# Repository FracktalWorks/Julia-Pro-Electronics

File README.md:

# Julia-Pro-Electronics
Eagle files and documentation for Julia Pro 3D Printers

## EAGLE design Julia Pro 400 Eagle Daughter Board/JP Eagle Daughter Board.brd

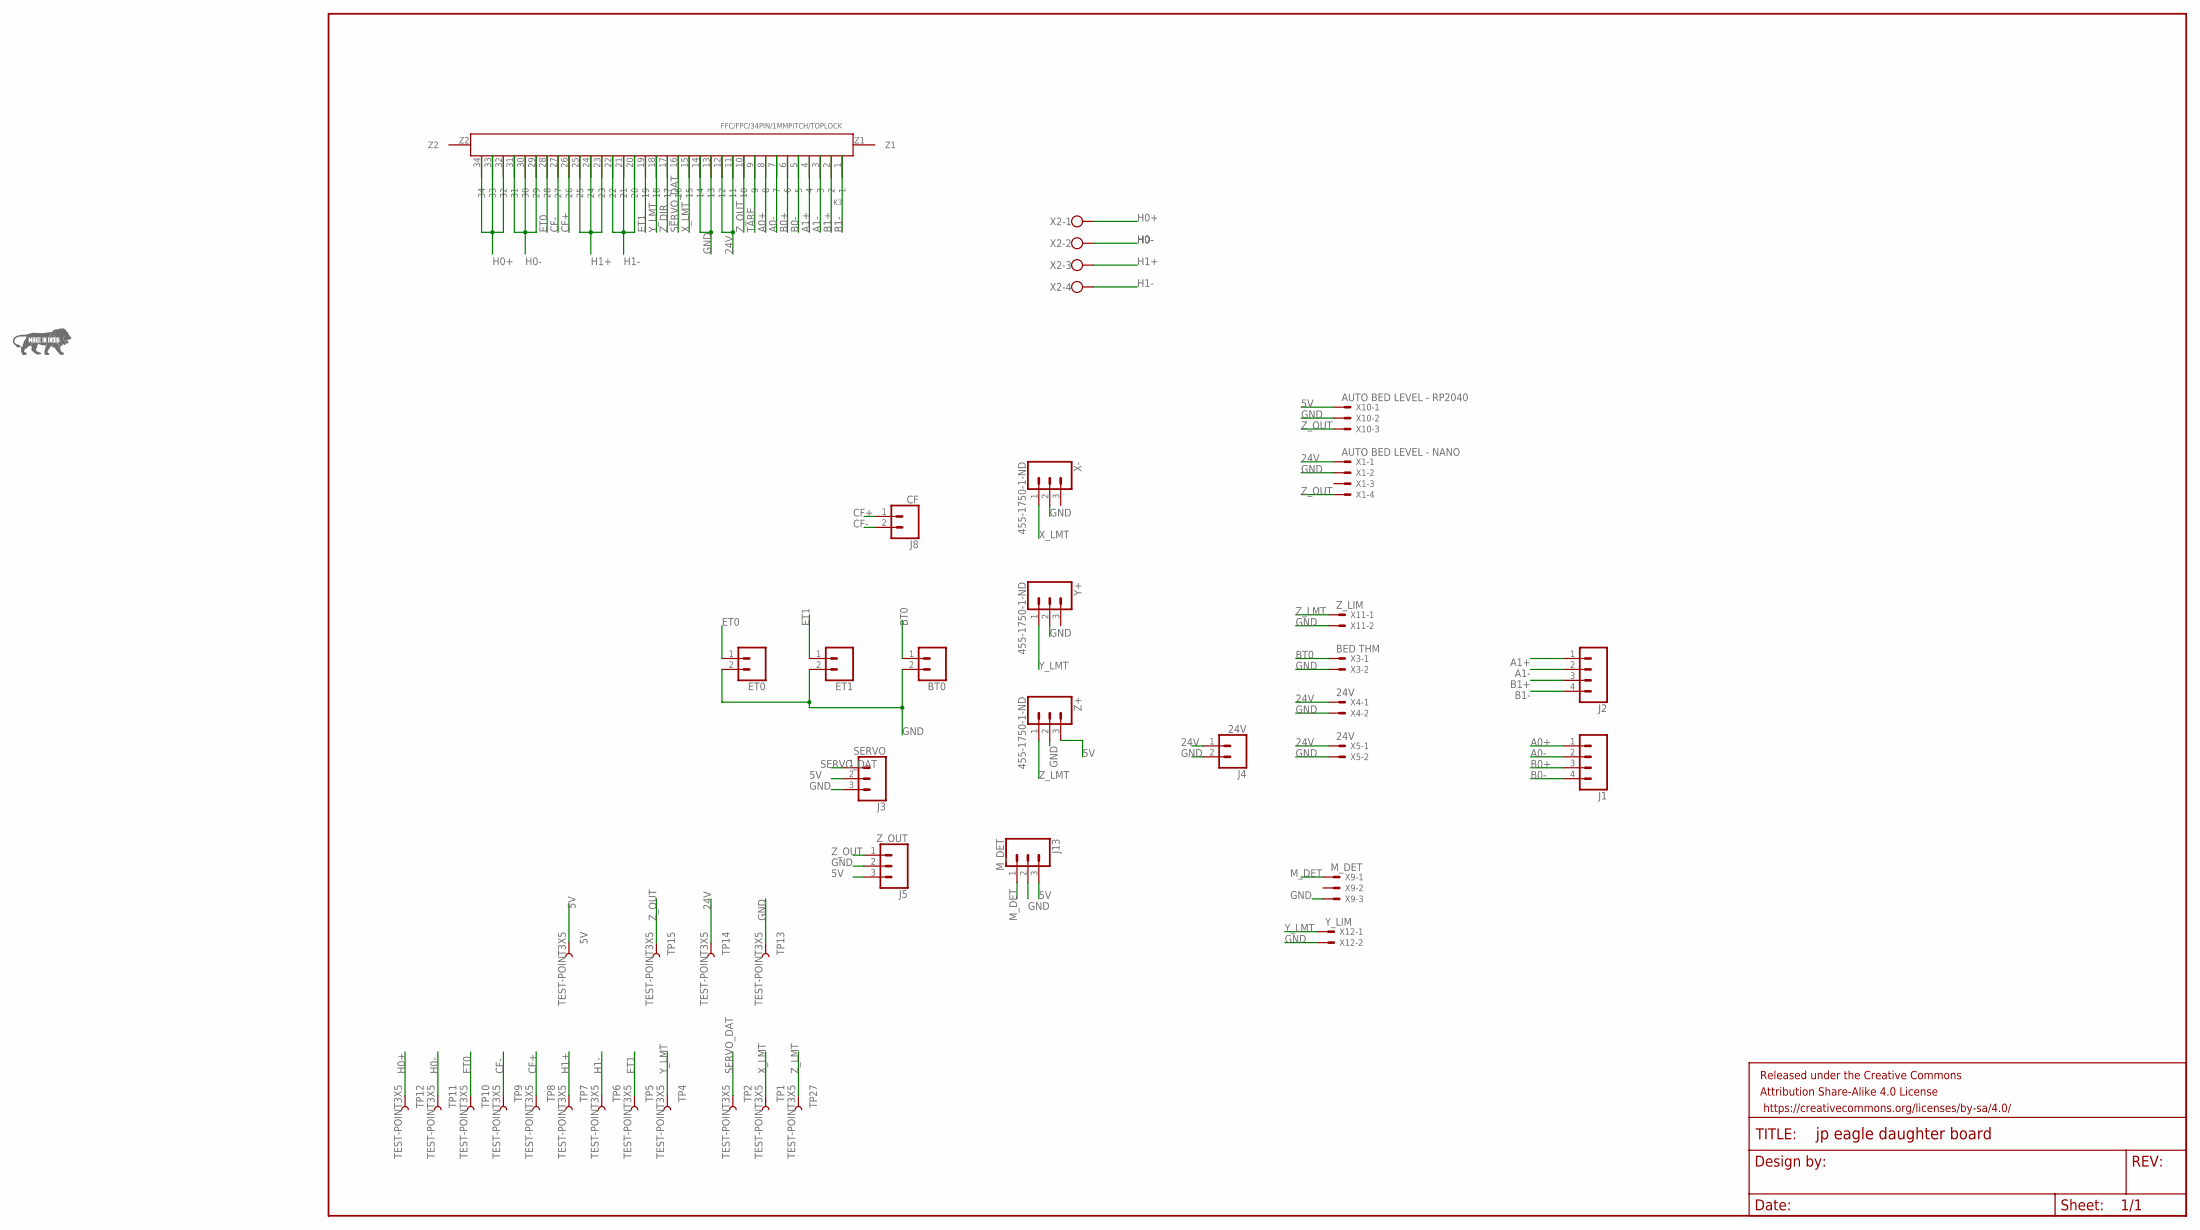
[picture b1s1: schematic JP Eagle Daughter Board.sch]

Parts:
5V: TEST-POINT3X5; PAD.03X.05
BT0: CONN_02; 1X02
ET0, ET1: CONN_02; 1X02
FRAME1: FRAME-LEDGER; CREATIVE_COMMONS
J1, J2: CONN_04; 1X04
J3: SERVO; 1X03
J4: 24V; 1X02
J5: Z_OUT; 1X03
J8: CF; 1X02
J13: M_DET; 1X03
K3: FFC/FPC/34PIN/1MMPITCH/TOPLOCK; 34PIN/1MMPITCH/FFC/FPC
TP1, TP2, TP4, TP5, TP6, TP7, TP8, TP9, TP10, TP11, TP12, TP13, TP14, TP15, TP27: TEST-POINT3X5; PAD.03X.05
U$2: MAKEININDIA
X1: AUTO BED LEVEL - NANO; JST-XH-04-PACKAGE-LONG-PAD
X2: W237-4
X3: BED THM; JST-XH-02-PACKAGE-LONG-PAD
X4, X5: 24V; JST-XH-02-PACKAGE-LONG-PAD
X9: M_DET; JST-XH-03-PACKAGE-LONG-PAD
X10: AUTO BED LEVEL - RP2040; JST-XH-03-PACKAGE-LONG-PAD
X11: Z_LIM; JST-XH-02-PACKAGE-LONG-PAD
X12: Y_LIM; JST-XH-02-PACKAGE-LONG-PAD
X-: 455-1750-1-ND; 1X03
Y+: 455-1750-1-ND; 1X03
Z+: 455-1750-1-ND; 1X03

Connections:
5V: 5V.P$1, J3.2, J5.3, J13.3, X10.1, Z+.3
24V: J4.1, K3.11, K3.12, TP14.P$1, X1.1, X4.1, X5.1
A0+: J1.1, K3.8
A0-: J1.2, K3.7
A1+: J2.1, K3.4
A1-: J2.2, K3.3
B0+: J1.3, K3.6
B0-: J1.4, K3.5
B1+: J2.3, K3.2
B1-: J2.4, K3.1
BT0: BT0.1, X3.1
CF+: J8.1, K3.26, TP8.P$1
CF-: J8.2, K3.27, TP9.P$1
ET0: ET0.1, K3.28, TP10.P$1
ET1: ET1.1, K3.19, TP5.P$1
GND: BT0.2, ET0.2, ET1.2, J3.3, J4.2, J5.2, J13.2, K3.13, K3.14, TP13.P$1, X1.2, X3.2, X4.2, X5.2, X9.3, X10.2, X11.2, X12.2, X-.2, Y+.2, Z+.2
H0+: K3.32, K3.33, K3.34, TP12.P$1, X2.1
H0-: K3.29, K3.30, K3.31, TP11.P$1, X2.2
H1+: K3.23, K3.24, K3.25, TP7.P$1, X2.3
H1-: K3.20, K3.21, K3.22, TP6.P$1, X2.4
M_DET: J13.1, X9.1
SERVO_DAT: J3.1, K3.16, TP2.P$1
TARE: K3.9
X_LMT: K3.15, TP1.P$1, X-.1
Y_LMT: K3.18, TP4.P$1, X12.1, Y+.1
Z_DIR: K3.17
Z_LMT: TP27.P$1, X11.1, Z+.1
Z_OUT: J5.1, K3.10, TP15.P$1, X1.4, X10.3

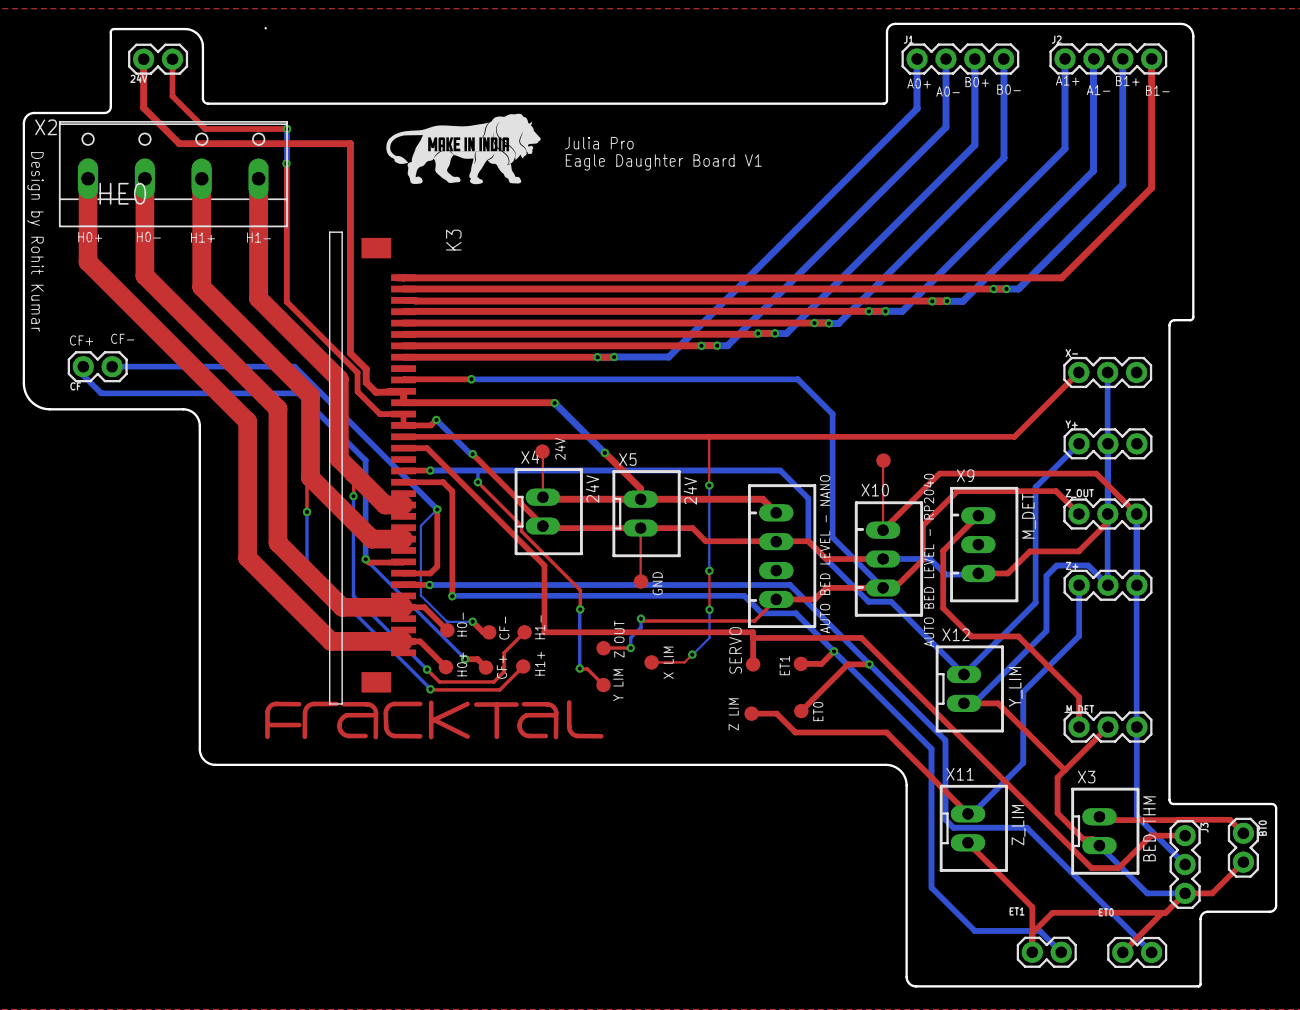
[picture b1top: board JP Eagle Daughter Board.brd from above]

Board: 2 copper layers, 110.2 x 84.7 mm, 42 parts (0 on the bottom side), 26 nets.

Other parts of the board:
U$1: FRACKTALLOGO

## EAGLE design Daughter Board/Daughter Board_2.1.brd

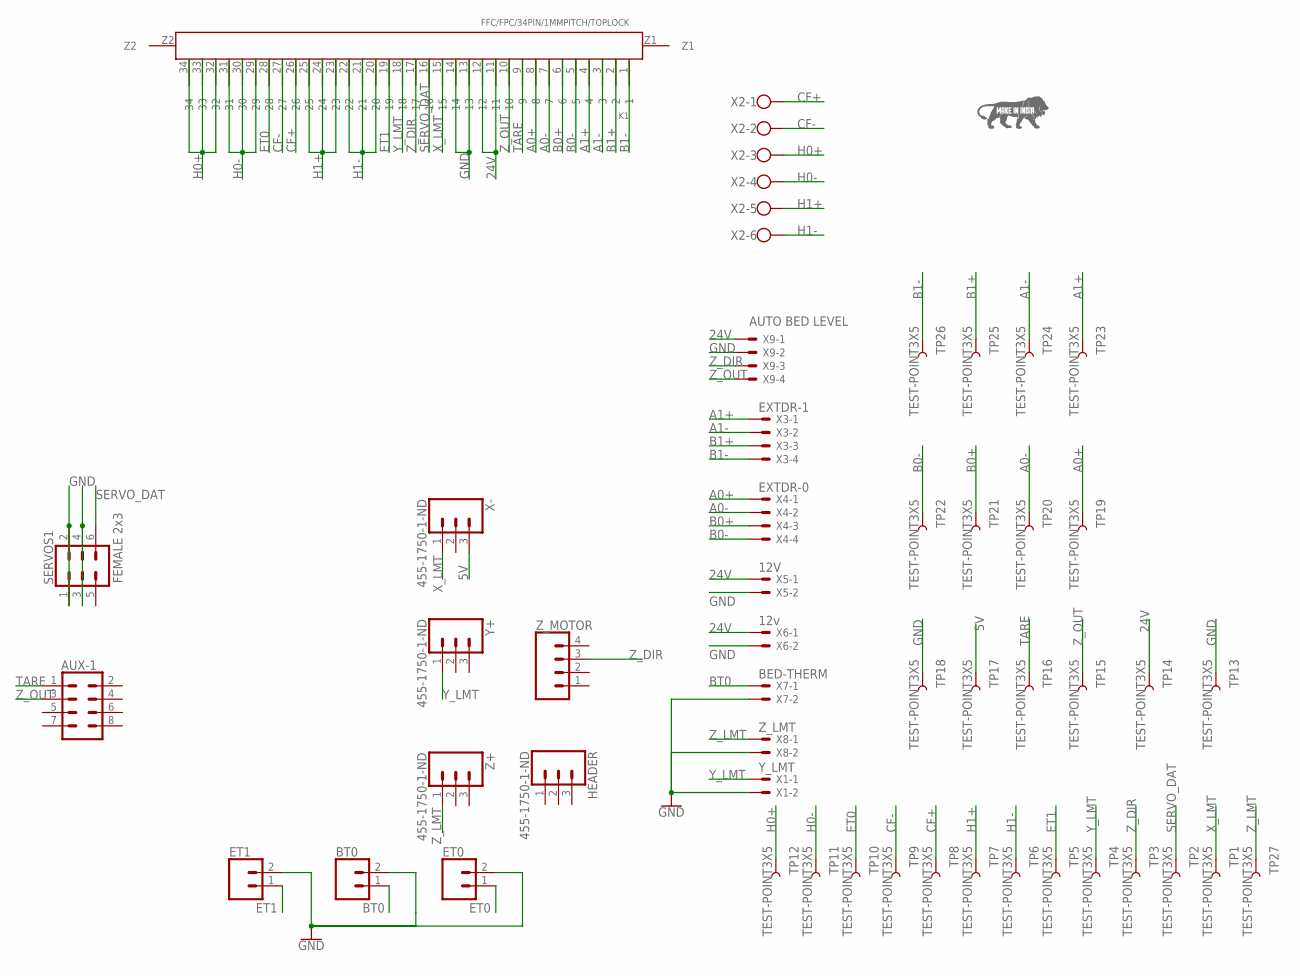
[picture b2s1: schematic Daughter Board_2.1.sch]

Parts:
AUX-1: CONN_04X2; 2X4
BT0: CONN_02; 1X02
ET0, ET1: CONN_02; 1X02
HEADER: 455-1750-1-ND; 1X03
K1: FFC/FPC/34PIN/1MMPITCH/TOPLOCK; 34PIN/1MMPITCH/FFC/FPC
SERVOS1: FEMALE 2x3; 2X3
TP1, TP2, TP3, TP4, TP5, TP6, TP7, TP8, TP9, TP10, TP11, TP12, TP13, TP14, TP15, TP16, TP17, TP18, TP19, TP20, TP21, TP22, TP23, TP24, TP25, TP26, TP27: TEST-POINT3X5; PAD.03X.05
U$2: MAKEININDIA
X1: Y_LMT; JST-XH-02-PACKAGE-LONG-PAD
X2: W237-6
X3: EXTDR-1; JST-XH-04-PACKAGE-LONG-PAD
X4: EXTDR-0; JST-XH-04-PACKAGE-LONG-PAD
X5: 12V; JST-XH-02-PACKAGE-LONG-PAD
X6: 12v; JST-XH-02-PACKAGE-LONG-PAD
X7: BED-THERM; JST-XH-02-PACKAGE-LONG-PAD
X8: Z_LMT; JST-XH-02-PACKAGE-LONG-PAD
X9: JST-XH-04-PIN-LONG-PAD; JST-XH-04-PACKAGE-LONG-PAD
X-: 455-1750-1-ND; 1X03
Y+: 455-1750-1-ND; 1X03
Z+: 455-1750-1-ND; 1X03
Z_MOTOR: CONN_04; 1X04

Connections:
5V: TP17.P$1, X-.3
24V: K1.11, K1.12, TP14.P$1, X5.1, X6.1, X9.1
A0+: K1.8, TP19.P$1, X4.1
A0-: K1.7, TP20.P$1, X4.2
A1+: K1.4, TP23.P$1, X3.1
A1-: K1.3, TP24.P$1, X3.2
B0+: K1.6, TP21.P$1, X4.3
B0-: K1.5, TP22.P$1, X4.4
B1+: K1.2, TP25.P$1, X3.3
B1-: K1.1, TP26.P$1, X3.4
BT0: BT0.1, X7.1
CF+: K1.26, TP8.P$1, X2.1
CF-: K1.27, TP9.P$1, X2.2
ET0: ET0.1, K1.28, TP10.P$1
ET1: ET1.1, K1.19, TP5.P$1
GND: BT0.2, ET0.2, ET1.2, K1.13, K1.14, SERVOS1.1, SERVOS1.2, TP13.P$1, TP18.P$1, X1.2, X5.2, X6.2, X7.2, X8.2, X9.2
H0+: K1.32, K1.33, K1.34, TP12.P$1, X2.3
H0-: K1.29, K1.30, K1.31, TP11.P$1, X2.4
H1+: K1.23, K1.24, K1.25, TP7.P$1, X2.5
H1-: K1.20, K1.21, K1.22, TP6.P$1, X2.6
unnamed: SERVOS1.3, SERVOS1.4
SERVO_DAT: K1.16, SERVOS1.6, TP2.P$1
TARE: AUX-1.1, K1.9, TP16.P$1
X_LMT: K1.15, TP1.P$1, X-.1
Y_LMT: K1.18, TP4.P$1, X1.1, Y+.1
Z_DIR: K1.17, TP3.P$1, X9.3, Z_MOTOR.3
Z_LMT: TP27.P$1, X8.1, Z+.1
Z_OUT: AUX-1.3, K1.10, TP15.P$1, X9.4

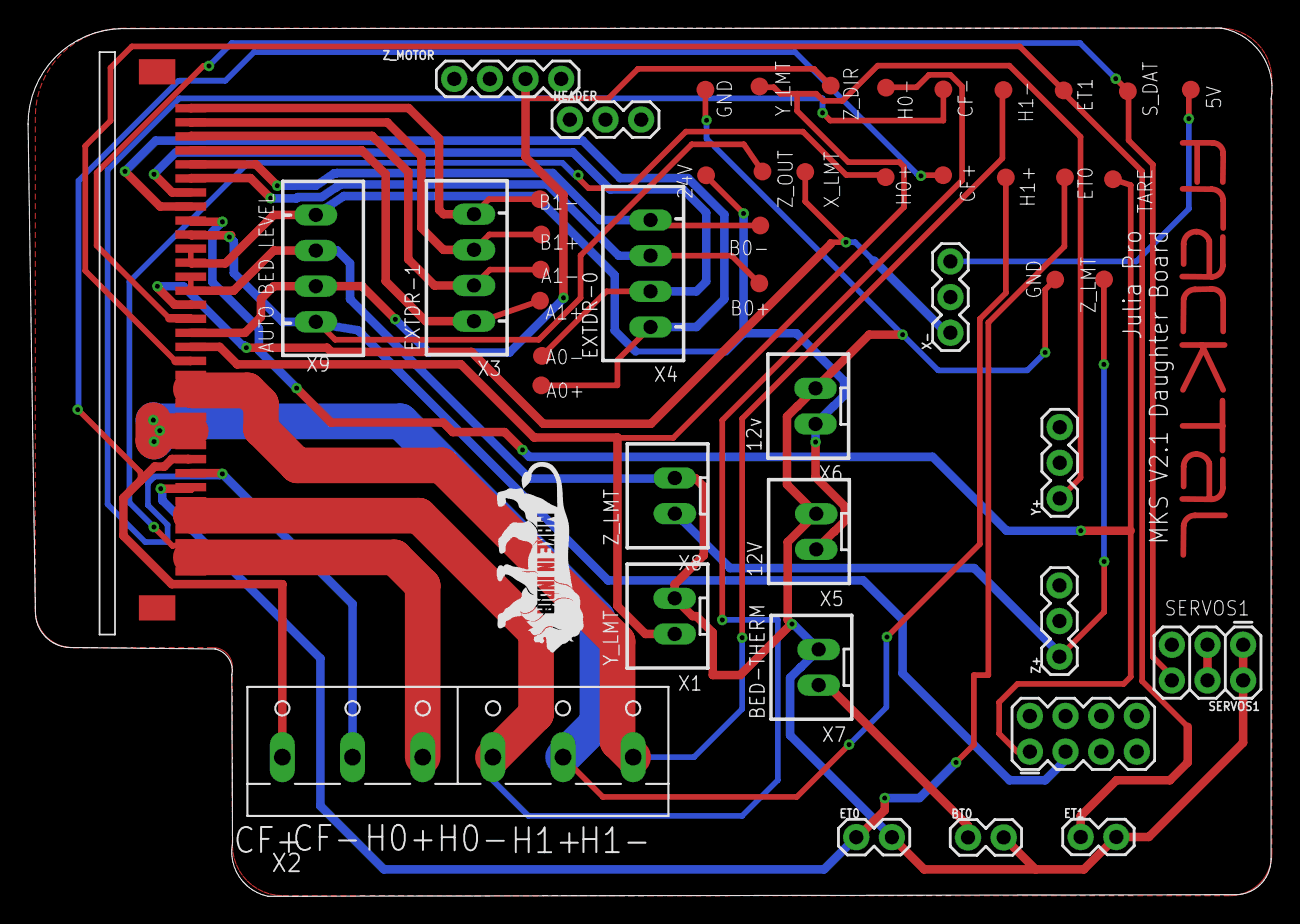
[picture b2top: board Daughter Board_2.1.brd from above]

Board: 2 copper layers, 88.6 x 61.9 mm, 49 parts (0 on the bottom side), 28 nets.

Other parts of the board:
U$1: FRACKTALLOGO

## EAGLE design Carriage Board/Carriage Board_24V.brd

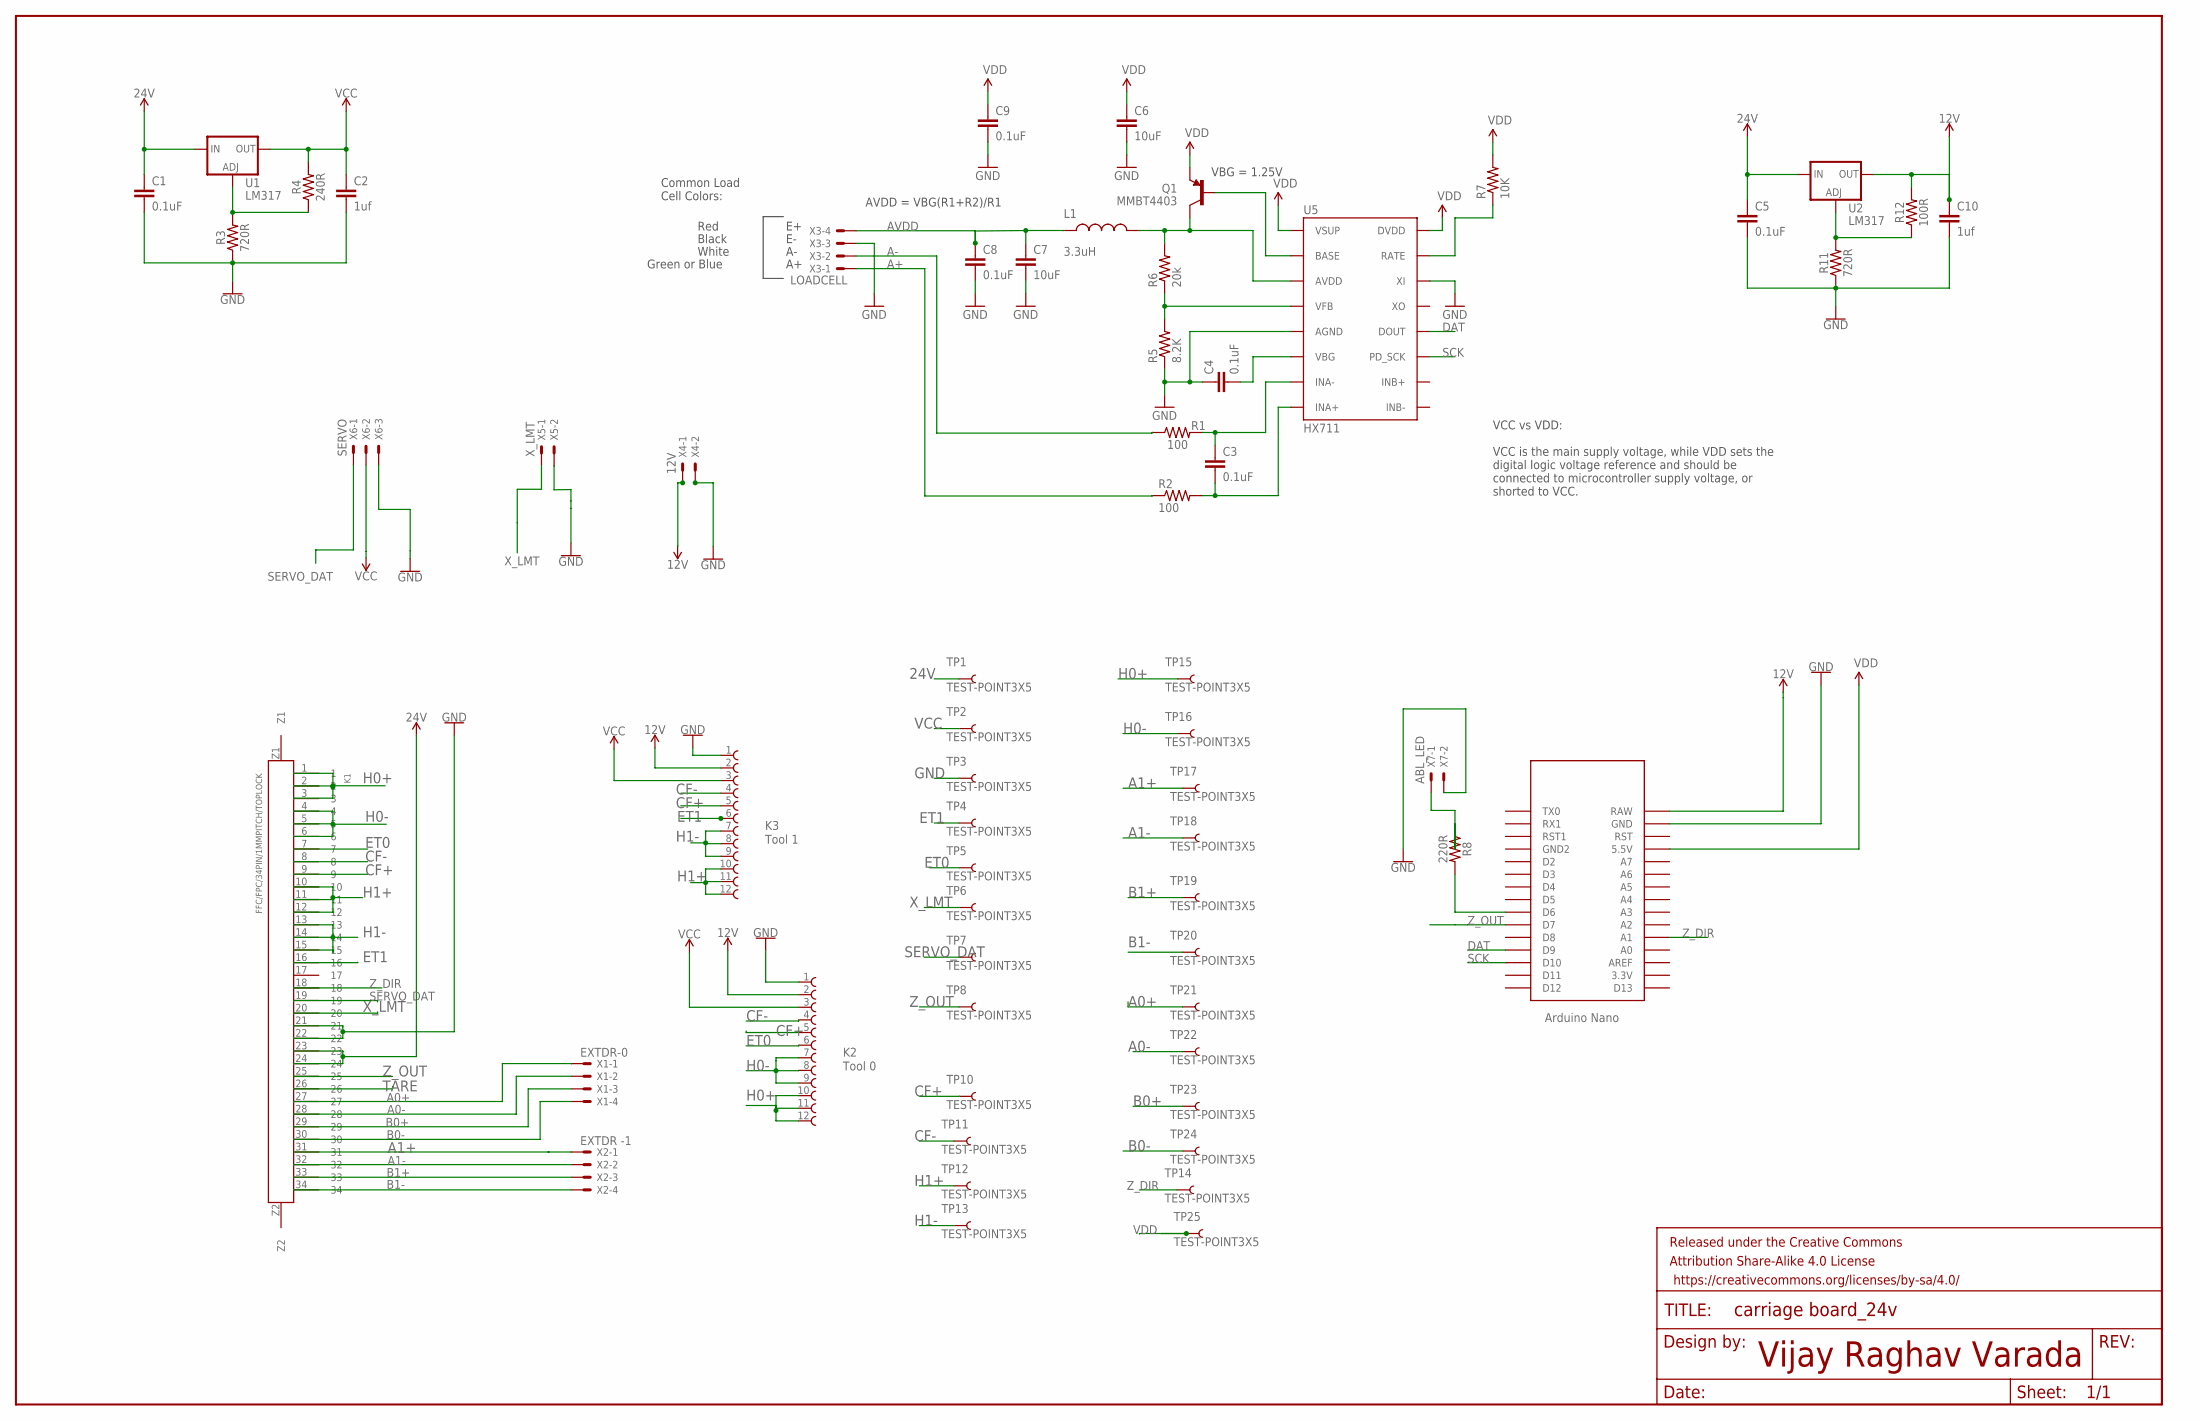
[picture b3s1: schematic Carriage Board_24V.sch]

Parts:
C1, C5: 0.1uF; 0603
C2, C10: 1uf; 0603
C3, C4, C8, C9: 0.1uF; 0603-CAP
C6, C7: 10uF; 1210
FRAME1: FRAME-LEDGER; CREATIVE_COMMONS
K1: FFC/FPC/34PIN/1MMPITCH/TOPLOCK; 34PIN/1MMPITCH/FFC/FPC
K2: Tool 0; 68611214122
K3: Tool 1; 68611214122
L1: 3.3uH; 0805
Q1: MMBT4403; SOT23-3
R1, R2: 100; 0603-RES
R3, R11: 720R; 0603
R4: 240R; 0603
R5: 8.2K; 0603-RES
R6: 20k; 0603-RES
R7: 10K; 0603-RES
R8: 220R; 0603
R12: 100R; 0603
TP1, TP2, TP3, TP4, TP5, TP6, TP7, TP8, TP10, TP11, TP12, TP13, TP14, TP15, TP16, TP17, TP18, TP19, TP20, TP21, TP22, TP23, TP24, TP25: TEST-POINT3X5; PAD.03X.05
U1, U2: LM317; SOT223
U5: HX711; SO16
U$1: NANO
X1: EXTDR-0; JST-XH-04-PACKAGE-LONG-PAD
X2: EXTDR -1; JST-XH-04-PACKAGE-LONG-PAD
X3: LOADCELL; JST-XH-04-PACKAGE-LONG-PAD
X4: 12V; JST-XH-02-PACKAGE-LONG-PAD
X5: X_LMT; JST-XH-02-PACKAGE-LONG-PAD
X6: SERVO; JST-XH-03-PACKAGE-LONG-PAD
X7: ABL_LED; JST-XH-02-PACKAGE-LONG-PAD

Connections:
12V: C10.1, R12.2, U2.2 (OUT), U$1.RAW
24V: C1.1, C5.1, K1.23, K1.24, K2.2, K3.2, TP1.P$1, U1.3 (IN), U2.3 (IN), X4.1
A0+: K1.27, TP21.P$1, X1.1
A0-: K1.28, TP22.P$1, X1.2
A1+: K1.31, TP17.P$1, X2.1
A1-: K1.32, TP18.P$1, X2.2
A+: R2.1, X3.1
A-: R1.1, X3.2
ADJ: R3.2, R4.1, U1.1 (ADJ)
ADJ1: R11.2, R12.1, U2.1 (ADJ)
AVDD: C7.1, C8.1, L1.1, X3.4
B0+: K1.29, TP23.P$1, X1.3
B0-: K1.30, TP24.P$1, X1.4
B1+: K1.33, TP19.P$1, X2.3
B1-: K1.34, TP20.P$1, X2.4
CF+: K1.9, K2.5, K3.5, TP10.P$1
CF-: K1.8, K2.4, K3.4, TP11.P$1
DAT: U5.12 (DOUT), U$1.D9
ET0: K1.7, K2.6, TP5.P$1
ET1: K1.16, K3.6, TP4.P$1
GND: C1.2, C2.2, C4.1, C5.2, C6.2, C7.2, C8.2, C9.2, C10.2, K1.21, K1.22, K2.1, K3.1, R3.1, R5.1, R11.1, TP3.P$1, U5.5 (AGND), U5.14 (XI), U$1.GND, X3.3, X4.2, X5.2, X6.3, X7.2
H0+: K1.1, K1.2, K1.3, K2.10, K2.11, K2.12, TP15.P$1
H0-: K1.4, K1.5, K1.6, K2.7, K2.8, K2.9, TP16.P$1
H1+: K1.10, K1.11, K1.12, K3.10, K3.11, K3.12, TP12.P$1
H1-: K1.13, K1.14, K1.15, K3.7, K3.8, K3.9, TP13.P$1
unnamed: R8.2, U$1.D6
unnamed: R7.1, U5.15 (RATE)
unnamed: C3.1, R1.2, U5.7 (INA-)
unnamed: Q1.1 (B), U5.2 (BASE)
unnamed: L1.2, Q1.3 (C), R6.2, U5.3 (AVDD)
unnamed: R5.2, R6.1, U5.4 (VFB)
unnamed: C4.2, U5.6 (VBG)
unnamed: C3.2, R2.2, U5.8 (INA+)
unnamed: R8.1, X7.1
SCK: U5.11 (PD_SCK), U$1.D10
SERVO_DAT: K1.19, TP7.P$1, X6.1
TARE: K1.26
VCC: C2.1, K2.3, K3.3, R4.2, TP2.P$1, U1.2 (OUT), X6.2
VDD: C6.1, C9.1, Q1.2 (E), R7.2, TP25.P$1, U5.1 (VSUP), U5.16 (DVDD), U$1.5V (5.5V)
X_LMT: K1.20, TP6.P$1, X5.1
Z_DIR: K1.18, TP14.P$1, U$1.A1
Z_OUT: K1.25, TP8.P$1, U$1.D7

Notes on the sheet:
VBG = 1.25V
AVDD = VBG(R1+R2)/R1
Red
Black
White
Green or Blue
Common Load Cell Colors:
VCC vs VDD: VCC is the main supply voltage, while VDD sets the digital logic voltage reference and should be connected to microcontroller supply voltage, or shorted to VCC.
Vijay Raghav Varada

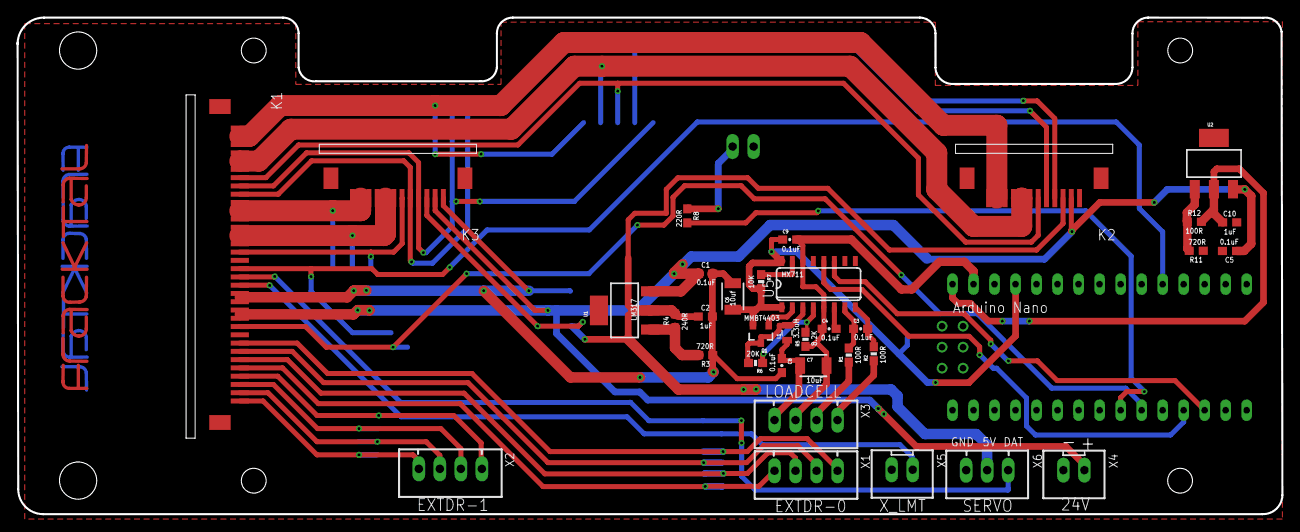
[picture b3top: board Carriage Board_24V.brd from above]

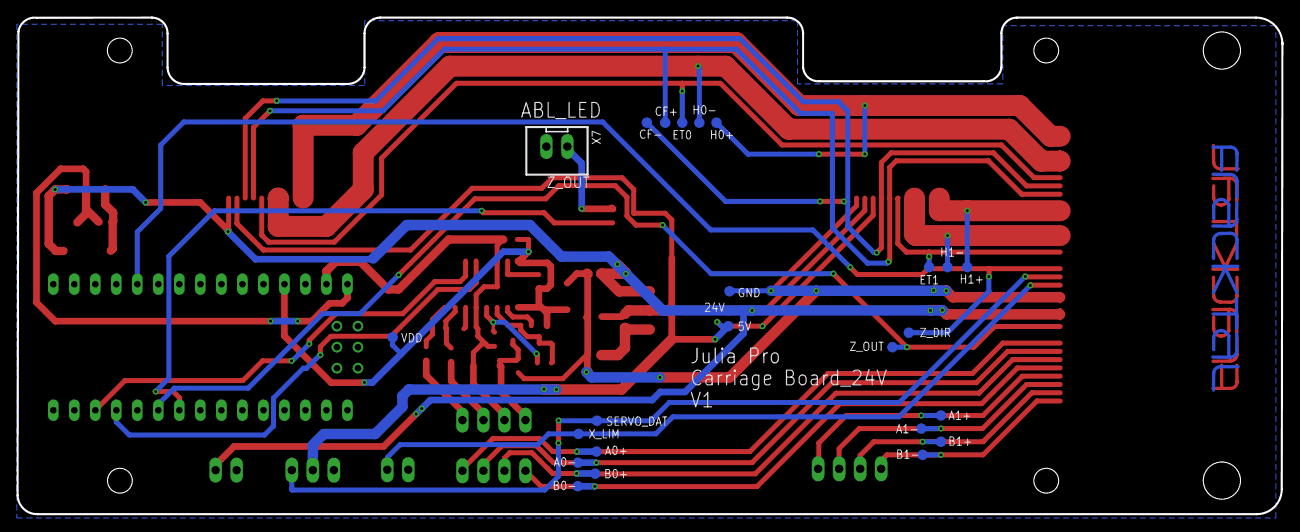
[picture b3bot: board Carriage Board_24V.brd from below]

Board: 2 copper layers, 152.9 x 60.0 mm, 63 parts (26 on the bottom side), 41 nets.

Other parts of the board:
U$2, U$3: FRACKTALLOGO

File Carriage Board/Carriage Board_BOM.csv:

"Part";"Value";"Device";"Package";"Description";"PROD_ID";"SF_SKU";"VALUE";
"C1";"470uF";"9.0PF-0603-50V-10%";"0603";"9.0pF ceramic capacitors";"CAP-09341";"";"9.0pF";
"C2";"1uf";"9.0PF-0603-50V-10%";"0603";"9.0pF ceramic capacitors";"CAP-09341";"";"9.0pF";
"C3";"0.1uF";"0.1UF-25V-5%(0603)";"0603-CAP";"CAP-08604";"CAP-08604";"";"0.1uF";
"C4";"0.1uF";"0.1UF-25V-5%(0603)";"0603-CAP";"CAP-08604";"CAP-08604";"";"0.1uF";
"C6";"10uF";"10UF50V20%(1210)";"1210";"CAP-09824";"CAP-09824";"";"10uF";
"C7";"10uF";"10UF50V20%(1210)";"1210";"CAP-09824";"CAP-09824";"";"10uF";
"C8";"0.1uF";"0.1UF-25V-5%(0603)";"0603-CAP";"CAP-08604";"CAP-08604";"";"0.1uF";
"C9";"0.1uF";"0.1UF-25V-5%(0603)";"0603-CAP";"CAP-08604";"CAP-08604";"";"0.1uF";
"D1";"Z_OUT";"LED3MM";"LED_3MM";"LED (Generic)";"DIO-08794";"";"";
"FRAME1";"FRAME-LEDGER";"FRAME-LEDGER";"CREATIVE_COMMONS";"Schematic Frame - Ledger";"";"";"";
"J3";"DEBUG";"CONN_02";"1X02";"Multi connection point. Often used as Generic Header-pin footprint for 0.1 inch spaced/style header connections";"";"";"";
"K1";"FFC/FPC/34PIN/1MMPITCH/TOPLOCK";"FFC/FPC/34PIN/1MMPITCH/TOPLOCK";"34PIN/1MMPITCH/FFC/FPC";"";"";"";"";
"K2";"Tool 0";"68611214122";"68611214122";"WR-FPC 1.00mm SMT ZIF Horizontal Top Contact, 12 Pins=>Code : Con_FPC_ZIF_1.00_68611214122";"";"";"";
"K3";"Tool 1";"68611214122";"68611214122";"WR-FPC 1.00mm SMT ZIF Horizontal Top Contact, 12 Pins=>Code : Con_FPC_ZIF_1.00_68611214122";"";"";"";
"L1";"3.3uH";"INDUCTOR0805-IND";"0805";"Inductors";"NDUC-13076";"";"";
"Q1";"MMBT4403";"TRANSISTOR_PNPMMBT4403";"SOT23-3";"Generic PNP BJT";"TRANS-09245";"";"MMBT4403";
"R1";"100";"100OHM-1/10W-1%(0603)";"0603-RES";"RES-07863";"RES-07863";"";"100";
"R2";"100";"100OHM-1/10W-1%(0603)";"0603-RES";"RES-07863";"RES-07863";"";"100";
"R3";" 720R";"RESISTOR0603";"0603";"Generic Resistor Package";" ";"";" ";
"R4";"240R";"RESISTOR0603";"0603";"Generic Resistor Package";" ";"";" ";
"R5";"8.2K";"8.2KOHM-1/10W-5%(0603)";"0603-RES";"RES-10646";"RES-10646";"";"";
"R6";"20k";"20KOHM1/10W1%(0603)";"0603-RES";"RES-09383";"RES-09383";"";"20k";
"R7";"10K";"10KOHM-1/10W-1%(0603)0603";"0603-RES";"RES-00824";"RES-00824";"";"10K";
"R8";"220R";"RESISTOR0603";"0603";"Generic Resistor Package";" ";"";" ";
"R9";"10K";"RESISTOR0603";"0603";"Generic Resistor Package";" ";"";" ";
"R10";"10K";"RESISTOR0603";"0603";"Generic Resistor Package";" ";"";" ";
"S1";"TARE";"MOMENTARY-SWITCH-SPST-PTH-6.0MM";"TACTILE_SWITCH_PTH_6.0MM";"Momentary Switch (Pushbutton) - SPST";" SWCH-08441";"COM-00097";"";
"TP1";"TEST-POINT3X5";"TEST-POINT3X5";"PAD.03X.05";"SparkFun Test Points";"";"";"";
"TP2";"TEST-POINT3X5";"TEST-POINT3X5";"PAD.03X.05";"SparkFun Test Points";"";"";"";
"TP3";"TEST-POINT3X5";"TEST-POINT3X5";"PAD.03X.05";"SparkFun Test Points";"";"";"";
"TP4";"TEST-POINT3X5";"TEST-POINT3X5";"PAD.03X.05";"SparkFun Test Points";"";"";"";
"TP5";"TEST-POINT3X5";"TEST-POINT3X5";"PAD.03X.05";"SparkFun Test Points";"";"";"";
"TP6";"TEST-POINT3X5";"TEST-POINT3X5";"PAD.03X.05";"SparkFun Test Points";"";"";"";
"TP7";"TEST-POINT3X5";"TEST-POINT3X5";"PAD.03X.05";"SparkFun Test Points";"";"";"";
"TP8";"TEST-POINT3X5";"TEST-POINT3X5";"PAD.03X.05";"SparkFun Test Points";"";"";"";
"TP9";"TEST-POINT3X5";"TEST-POINT3X5";"PAD.03X.05";"SparkFun Test Points";"";"";"";
"TP10";"TEST-POINT3X5";"TEST-POINT3X5";"PAD.03X.05";"SparkFun Test Points";"";"";"";
"TP11";"TEST-POINT3X5";"TEST-POINT3X5";"PAD.03X.05";"SparkFun Test Points";"";"";"";
"TP12";"TEST-POINT3X5";"TEST-POINT3X5";"PAD.03X.05";"SparkFun Test Points";"";"";"";
"TP13";"TEST-POINT3X5";"TEST-POINT3X5";"PAD.03X.05";"SparkFun Test Points";"";"";"";
"TP14";"TEST-POINT3X5";"TEST-POINT3X5";"PAD.03X.05";"SparkFun Test Points";"";"";"";
"TP15";"TEST-POINT3X5";"TEST-POINT3X5";"PAD.03X.05";"SparkFun Test Points";"";"";"";
"TP16";"TEST-POINT3X5";"TEST-POINT3X5";"PAD.03X.05";"SparkFun Test Points";"";"";"";
"TP17";"TEST-POINT3X5";"TEST-POINT3X5";"PAD.03X.05";"SparkFun Test Points";"";"";"";
"TP18";"TEST-POINT3X5";"TEST-POINT3X5";"PAD.03X.05";"SparkFun Test Points";"";"";"";
"TP19";"TEST-POINT3X5";"TEST-POINT3X5";"PAD.03X.05";"SparkFun Test Points";"";"";"";
"TP20";"TEST-POINT3X5";"TEST-POINT3X5";"PAD.03X.05";"SparkFun Test Points";"";"";"";
"TP21";"TEST-POINT3X5";"TEST-POINT3X5";"PAD.03X.05";"SparkFun Test Points";"";"";"";
"TP22";"TEST-POINT3X5";"TEST-POINT3X5";"PAD.03X.05";"SparkFun Test Points";"";"";"";
"TP23";"TEST-POINT3X5";"TEST-POINT3X5";"PAD.03X.05";"SparkFun Test Points";"";"";"";
"TP24";"TEST-POINT3X5";"TEST-POINT3X5";"PAD.03X.05";"SparkFun Test Points";"";"";"";
"U$1";"NANO";"NANO";"NANO";"Arduino Nano";"";"";"";
"U$2";"FWLOGO";"FWLOGO";"FWLOGO";"";"";"";"";
"U1";"LM317";"V_REG_317SMD";"SOT223";"Voltage Regulator";"";"";"";
"U5";"HX711";"HX711HX711";"SO16";"";"IC-12445";"";"HX711";
"X1";"EXTDR-0";"JST-XH-04-PIN-LONG-PAD";"JST-XH-04-PACKAGE-LONG-PAD";"JST XH Connector 2 Pin";"";"";"";
"X2";"EXTDR -1";"JST-XH-04-PIN-LONG-PAD";"JST-XH-04-PACKAGE-LONG-PAD";"JST XH Connector 2 Pin";"";"";"";
"X3";"LOADCELL";"JST-XH-04-PIN-LONG-PAD";"JST-XH-04-PACKAGE-LONG-PAD";"JST XH Connector 2 Pin";"";"";"";
"X4";"12V";"JST-XH-02-PIN-LONG-PAD";"JST-XH-02-PACKAGE-LONG-PAD";"JST XH Connector 2 Pin";"";"";"";
"X5";"X_LMT";"JST-XH-02-PIN-LONG-PAD";"JST-XH-02-PACKAGE-LONG-PAD";"JST XH Connector 2 Pin";"";"";"";
"X6";"SERVO";"JST-XH-03-PIN-LONG-PAD";"JST-XH-03-PACKAGE-LONG-PAD";"JST XH Connector 2 Pin";"";"";"";

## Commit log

2022-01-25 boards for GEN L 2.1
2024-08-27 Added Eagle Daughter Board
2024-08-27 Increased clearnace
2024-08-27 Update JP Eagle Daughter Board.brd
    Ground pour added

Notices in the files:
parts and their libraries:
SparkFun-Capacitors: Licensing: Creative Commons ShareAlike 4.0 International - https://creativecommons.org/licenses/by-sa/4.0
SparkFun-Connectors: Licensing: CC v3.0 Share-Alike You are welcome to use this library for commercial purposes.
SparkFun-Aesthetics: Released under the Creative Commons
